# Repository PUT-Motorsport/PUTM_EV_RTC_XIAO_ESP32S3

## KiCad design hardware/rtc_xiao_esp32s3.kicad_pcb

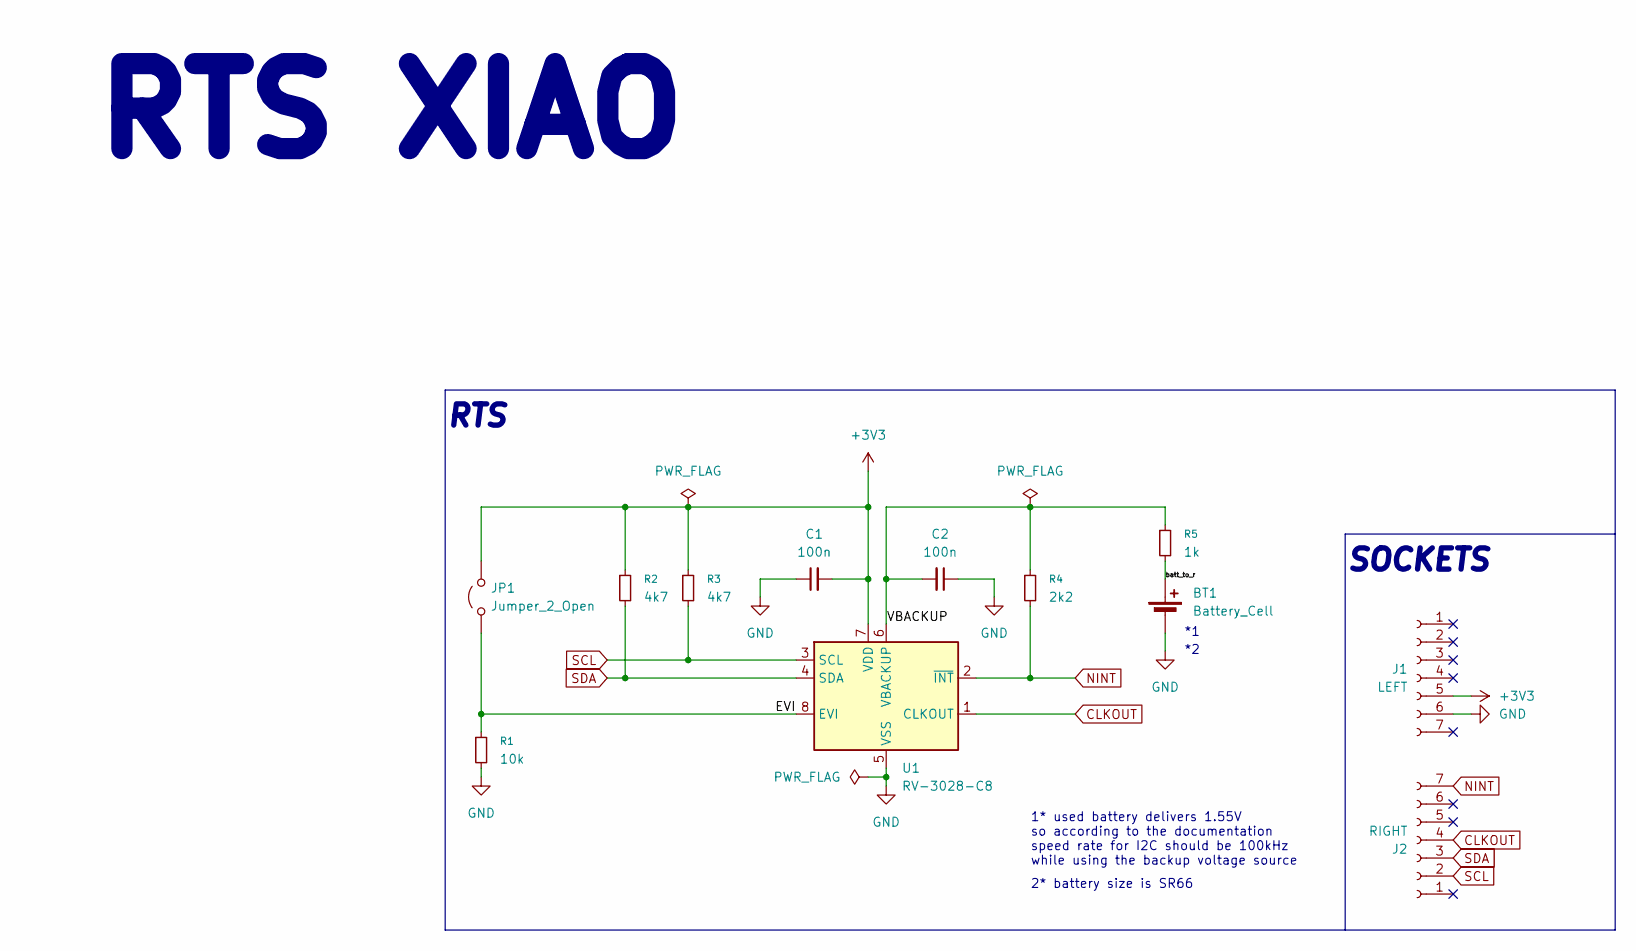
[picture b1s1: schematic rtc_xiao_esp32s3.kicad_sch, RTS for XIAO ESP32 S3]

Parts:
BT1: Battery_Cell; BatteryHolder_Keystone_2998_1x6.8mm; Mouser Part Number 534-2998
C1, C2: 100n; C_0603_1608Metric_Pad1.08x0.95mm_HandSolder; Mouser Part Number GRM033R6YA104ME14D
J1: LEFT; PinHeader_1x07_P2.54mm_Vertical
J2: RIGHT; PinHeader_1x07_P2.54mm_Vertical
JP1: Jumper_2_Open; SolderJumper-2_P1.3mm_Bridged_RoundedPad1.0x1.5mm
R1: 10k; R_0603_1608Metric_Pad0.98x0.95mm_HandSolder; Mouser Part Number 71-CRCW060310K0FKEE
R2, R3: 4k7; R_0603_1608Metric_Pad0.98x0.95mm_HandSolder; Mouser Part Number 71-CRCW06034K70FKEBC
R4: 2k2; R_0603_1608Metric_Pad0.98x0.95mm_HandSolder; Mouser Part Number 71-CRCW06032K20JNEBC
R5: 1k; R_0603_1608Metric_Pad0.98x0.95mm_HandSolder; Mouser Part Number 71-CRCW06031K00FKED
U1: RV-3028-C8; RV3028C832768kHz1PPMTAQC; Mouser Part Number 428-RV3028C81PPMTAQC

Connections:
+3V3: C1.2, J1.5, JP1.2 (B), R2.1, R3.1, U1.7 (VDD)
/EVI: JP1.1 (A), R1.1, U1.8 (EVI)
/VBACKUP: C2.2, R4.1, R5.1, U1.6 (VBACKUP)
/batt_to_r: BT1.1 (+), R5.2
CLKOUT: J2.4, U1.1 (CLKOUT)
GND: BT1.2 (-), C1.1, C2.1, J1.6, R1.2, U1.5 (VSS)
NINT: J2.7, R4.2, U1.2 (~INT)
SCL: J2.2, R3.2, U1.3 (SCL)
SDA: J2.3, R2.2, U1.4 (SDA)

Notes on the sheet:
RTS
SOCKETS
RTS XIAO
2* battery size is SR66
1* used battery delivers 1.55V so according to the documentation speed rate for I2C should be 100kHz while using the backup voltage source

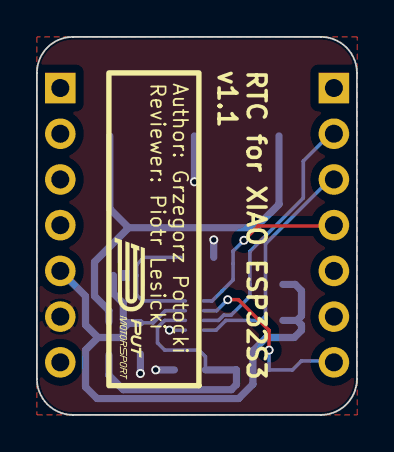
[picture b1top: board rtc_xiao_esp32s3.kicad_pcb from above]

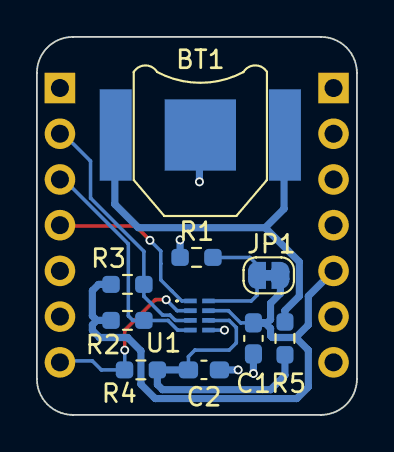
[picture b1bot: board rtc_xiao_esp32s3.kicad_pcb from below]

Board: 4 copper layers, 17.8 x 21.0 mm, 12 parts (10 on the bottom side), 9 nets.

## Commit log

2025-11-25 schematic & pcb added
2025-11-29 pcb update - routing
2025-11-29 pcb update
2025-12-16 minor changes
2026-01-03 gerber files added
2026-01-03 minor adjustments
2026-03-11 schematic update - useful notes added
2026-04-13 nowe sockety 2.54mm
2026-04-23 update to kicad10 & pcb dimension adjusted, changed pinout - 5V removed, 3v3 added
2026-04-28 5V flag removed, battery holder links added, new gerber files and zip
